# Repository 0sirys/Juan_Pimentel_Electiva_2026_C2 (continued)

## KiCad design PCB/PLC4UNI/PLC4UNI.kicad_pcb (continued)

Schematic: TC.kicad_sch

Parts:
C23, C24, C25, C26, C27: 100nF; C_0603_1608Metric
R51, R52: 0R; R_0603_1608Metric
R53: 20K; R_0603_1608Metric
R54, R55, R56, R57: 150R; R_0603_1608Metric
U15: MAX31856MUD+; TSSOP-14_L5.0-W4.4-P0.65-LS6.4-BL; MPN MAX31856MUD+; LCSC Part C116632

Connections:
3.3V: C26.1, C27.1, U15.5 (AVDD), U15.8 (DVDD); also elsewhere on the board
/plc4uni_top/CON_IN_TC+: R52.2; also elsewhere on the board
/plc4uni_top/CON_IN_TC-: R51.1, R53.1; also elsewhere on the board
/plc4uni_top/SPI_CLK: R56.2; also elsewhere on the board
/plc4uni_top/SPI_MISO: R55.2; also elsewhere on the board
/plc4uni_top/SPI_MOSI: R54.2; also elsewhere on the board
/plc4uni_top/TC/~DRDY: U15.7 (~DRDY)
/plc4uni_top/TC_FAULT: U15.13 (~FAULT); also elsewhere on the board
/plc4uni_top/TEMP_CS: R57.2; also elsewhere on the board
GND: C24.2, C25.2, C26.2, C27.2, U15.1 (AGND), U15.14 (DGND); also elsewhere on the board
unnamed: R53.2, U15.2 (BIAS)
unnamed: R56.1, U15.10 (SCK)
unnamed: R54.1, U15.12 (SDI)
unnamed: R55.1, U15.11 (SDO)
unnamed: C23.2, C24.1, R52.1, U15.4 (T+)
unnamed: C23.1, C25.1, R51.2, U15.3 (T-)
unnamed: R57.1, U15.9 (~CS)

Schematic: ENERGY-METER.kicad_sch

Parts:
C34, C35: 33nF; C_0603_1608Metric
C36: 68nF; C_0603_1608Metric
C37, C38, C39: 100nF; C_0603_1608Metric
R61, R62: R51; R_0805_2012Metric
R63, R66, R67, R68, R69: 390k; R_0603_1608Metric
R64: 1K; R_0603_1608Metric
R65: 1k; R_0603_1608Metric
R70: 510; R_0603_1608Metric
R71, R72, R73, R74: R_0603; R_0603_1608Metric
TP5, TP6, TP7: TestPoint; TestPoint_Pad_D4.0mm
U18: BL0942; SSOP-10_L4.9-W3.9-P1.00-LS6.0-BL; MPN BL0942; LCSC Part C2837510
U19: B0303S-1WR3_C7465185; PWRM-TH_BXXXXS-1WR3; MPN B0303S-1WR3; LCSC Part C7465185
U20: ISO7021DR; SOIC-8_L4.9-W3.9-P1.27-LS6.0-BL; MPN ISO7021DR; LCSC Part C2867957

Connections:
3.3V: C39.1, R73.1, R74.1, U19.2 (+Vin), U20.1 (VCC1); also elsewhere on the board
3.3V_P: C37.1, C38.1, R71.1, R72.1, TP7.1 (1_1), U18.1 (VDD), U18.8 (SCLK_BPS), U19.4 (+Vout), U20.8 (VCC2)
/plc4uni_top/CON-IN_CT_N: R62.2, R65.1; also elsewhere on the board
/plc4uni_top/CON-IN_CT_P: R61.1, R64.1; also elsewhere on the board
/plc4uni_top/CON_IN_VAC-P: R63.1; also elsewhere on the board
/plc4uni_top/EMRX: R73.2, U20.3 (INB); also elsewhere on the board
/plc4uni_top/EM_TX: R74.2, U20.2 (OUTA); also elsewhere on the board
Earth: C34.2, C35.1, C36.2, C37.2, C38.2, R61.2, R62.1, R70.1, U18.5 (GND), U18.7 (SEL), U19.3 (-Vout), U20.5 (GND2); also elsewhere on the board
GND: C39.2, U19.1 (-Vin), U20.4 (GND1); also elsewhere on the board
unnamed: R63.2, R66.1
unnamed: R66.2, R67.1
unnamed: R67.2, R68.1
unnamed: R68.2, R69.1
unnamed: C35.2, R65.2, TP6.1 (1_1), U18.3 (IN)
unnamed: C34.1, R64.2, TP5.1 (1_1), U18.2 (IP)
unnamed: R71.2, U18.9 (RX/SDI), U20.6 (OUTB)
unnamed: R72.2, U18.10 (TX/SDO), U20.7 (INA)
unnamed: C36.1, R69.2, R70.2, U18.4 (VP)

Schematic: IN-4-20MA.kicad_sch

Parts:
C5: 100nF; C_0603_1608Metric
C6: 47pF; C_0603_1608Metric
D13: 1N5819HW-7-F; SOD-123_L2.7-W1.6-LS3.7-RD; MPN 1N5819HW-7-F; LCSC Part C82544
D14: PESD5Z3.3; D_SOD-523
R15: 49.9R; R_0805_2012Metric; Tolerancia 0.1%
R16: 120R; R_0805_2012Metric; Tolerancia 0.1%
R17, R18: R_0805; R_0805_2012Metric

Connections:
/plc4uni_top/CON_IN_4-20MA_1: R15.1; also elsewhere on the board
/plc4uni_top/IN-4-20MA/OUT: C6.1, D14.1 (K), R18.2; also elsewhere on the board
GND: C5.2, C6.2, D13.2, D14.2 (A), R16.1; also elsewhere on the board
unnamed: C5.1, R17.2, R18.1
unnamed: D13.1, R15.2, R16.2, R17.1

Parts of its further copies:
C7: 100nF; C_0603_1608Metric
C8: 47pF; C_0603_1608Metric
D15: 1N5819HW-7-F; SOD-123_L2.7-W1.6-LS3.7-RD; MPN 1N5819HW-7-F; LCSC Part C82544
D16: PESD5Z3.3; D_SOD-523
R19: 49.9R; R_0805_2012Metric; Tolerancia 0.1%
R20: 120R; R_0805_2012Metric; Tolerancia 0.1%
R21, R22: R_0805; R_0805_2012Metric

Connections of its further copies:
/plc4uni_top/CON_IN_4-20MA_2: R19.1; also elsewhere on the board
/plc4uni_top/IN-4-20MA1/OUT: C8.1, D16.1 (K), R22.2; also elsewhere on the board
GND: C8.2, D15.2, D16.2 (A), R20.1; also elsewhere on the board
unnamed: C7.1, R21.2, R22.1
unnamed: D15.1, R19.2, R20.2, R21.1

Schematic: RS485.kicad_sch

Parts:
D35, D36, D37: SMBJ12CA; D_SMB_TVS
R75, R76: 10k; R_0603_1608Metric
R77, R78: 1k; R_0603_1608Metric
U23: TD301M485_C5451847; COMM-TH_TD301M485; MPN TD301M485; LCSC Part C5451847

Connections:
3.3V: R75.1, R76.1, U23.4 (VCC); also elsewhere on the board
/plc4uni_top/CON_RS485_A: D35.2 (A), D36.1 (K), R78.1, U23.7 (B); also elsewhere on the board
/plc4uni_top/CON_RS485_B: D36.2 (A), D37.2 (A), R77.2, U23.6 (A); also elsewhere on the board
/plc4uni_top/CON_RS485_G: D35.1 (K), D37.1 (K), R78.2, U23.5 (RGND); also elsewhere on the board
/plc4uni_top/RS485-RX: R76.2, U23.1 (RXD); also elsewhere on the board
/plc4uni_top/RS485-TX: R75.2, U23.2 (TXD); also elsewhere on the board
GND: U23.3 (GND); also elsewhere on the board
unnamed: R77.1, U23.8 (VO)

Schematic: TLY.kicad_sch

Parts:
K1, K2: G5V-1-DC3; RELAY-TH_G5V-1; MPN G5V-1 DC3; LCSC Part C397232
U8: LK1802; SOT-23-6_L2.9-W1.6-P0.95-LS2.8-BR; MPN LK1802; LCSC Part C2984831

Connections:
/plc4uni_top/CON_OUT_RLY1-COM: K1.5; also elsewhere on the board
/plc4uni_top/CON_OUT_RLY1-NC: K1.1; also elsewhere on the board
/plc4uni_top/CON_OUT_RLY1-NO: K1.10; also elsewhere on the board
/plc4uni_top/CON_OUT_RLY2-COM: K2.5; also elsewhere on the board
/plc4uni_top/CON_OUT_RLY2-NC: K2.1; also elsewhere on the board
/plc4uni_top/CON_OUT_RLY2-NO: K2.10; also elsewhere on the board
/plc4uni_top/OUT_RLY1: U8.3 (1B); also elsewhere on the board
/plc4uni_top/OUT_RLY2: U8.4 (2B); also elsewhere on the board
GND: U8.2 (E); also elsewhere on the board
VCC: K1.2, K2.2, U8.5 (COM); also elsewhere on the board

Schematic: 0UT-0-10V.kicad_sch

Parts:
C28, C29: 1uF; C_0603_1608Metric
C30: 100nF; C_0603_1608Metric
D27: SMBJ12CA; D_SMB_TVS
U16: GP8211S-TC50-EW; ESOP-8_L4.9-W3.9-P1.27-LS6.0-BL-EP; MPN GP8211S-TC50-EW; LCSC Part C3152008

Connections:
/plc4uni_top/CON_OUT_0-10V_1: C30.1, D27.2 (A), U16.6 (VOUT); also elsewhere on the board
/plc4uni_top/I2C_SCK: U16.1 (SCLK); also elsewhere on the board
/plc4uni_top/I2C_SDA: U16.2 (SDA); also elsewhere on the board
GND: C28.2, C29.2, C30.2, D27.1 (K), U16.5 (GND), U16.9 (EP); also elsewhere on the board
unnamed: C29.1, U16.8 (V5V)
VCC: C28.1, U16.4 (VCC); also elsewhere on the board

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
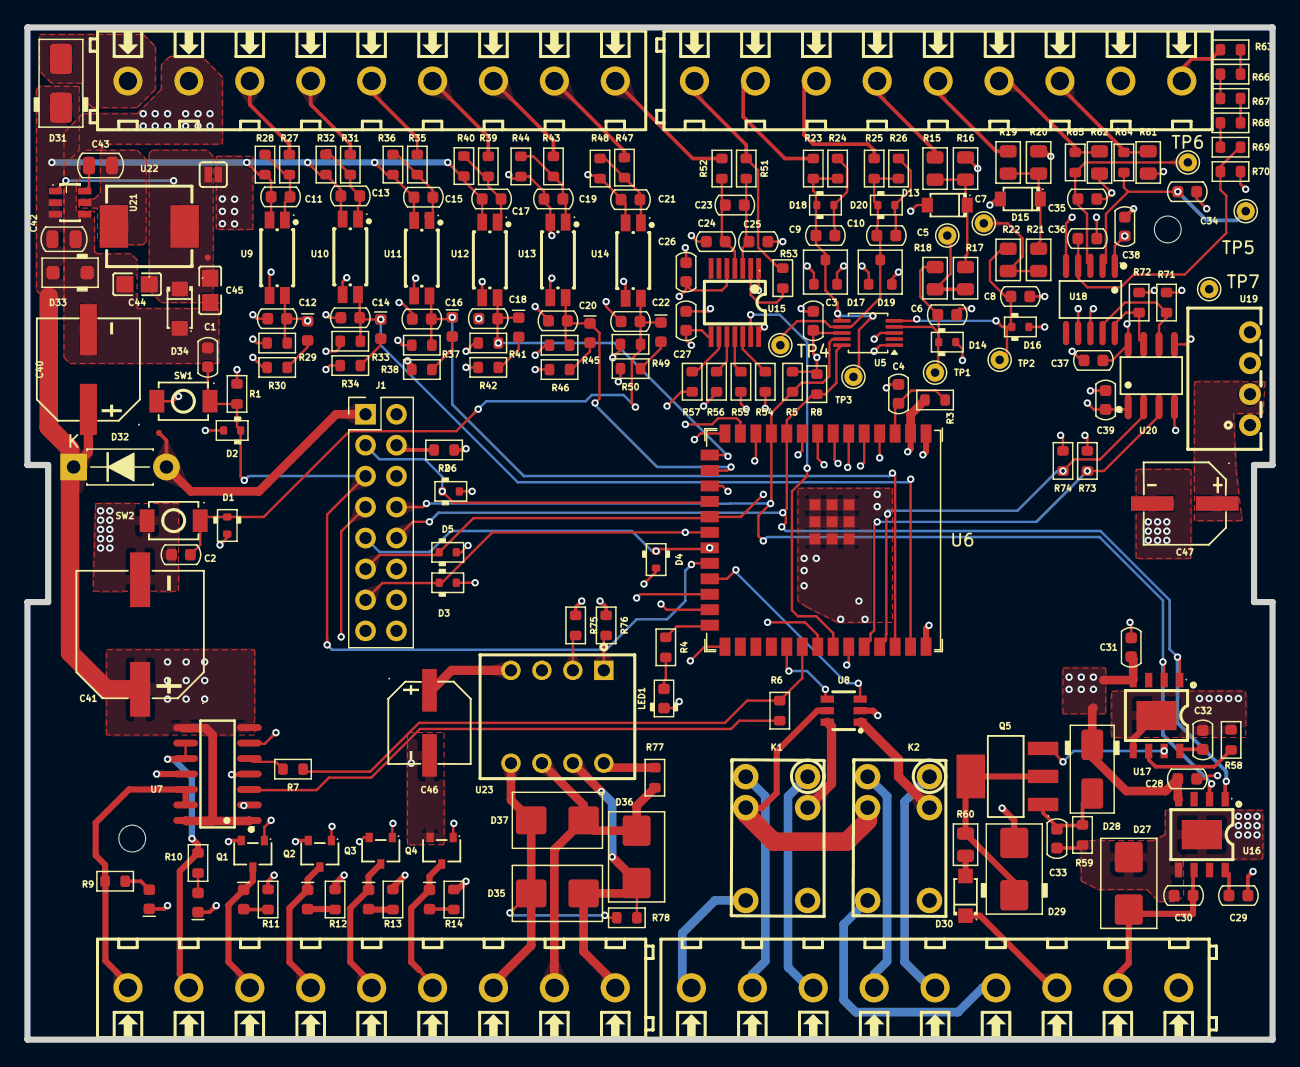
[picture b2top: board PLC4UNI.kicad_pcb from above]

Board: 4 copper layers, 102.2 x 83.1 mm, 209 parts (0 on the bottom side), 134 nets.

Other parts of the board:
H1, H2: MountingHole; MountingHole_2.2mm_M2_DIN965

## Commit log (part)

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2026-06-11 add git ignore
2026-06-11 Tarea 2 Done
2026-06-11 change name gitignore
2026-06-11 modify gitignore, ignore FCBak
2026-06-18 Tarea 2 Realizada
2026-06-18 Agregar salidas
2026-06-18 Tarea3 realizada
2026-06-18 Assembly Tarea 2
